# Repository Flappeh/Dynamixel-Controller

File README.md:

# Custom-Dynamixel-Controller
ESP32 Based Dynamixel Controller for MX-Series

This is a Custom Controller for Dynamixel MX-Series Servos that uses Dynamixel Protocol 1.0.

This Project Consists of 3 main components:
1. PCB

2. ESP32 Custom Firmware
3. .NET Core 3 Application

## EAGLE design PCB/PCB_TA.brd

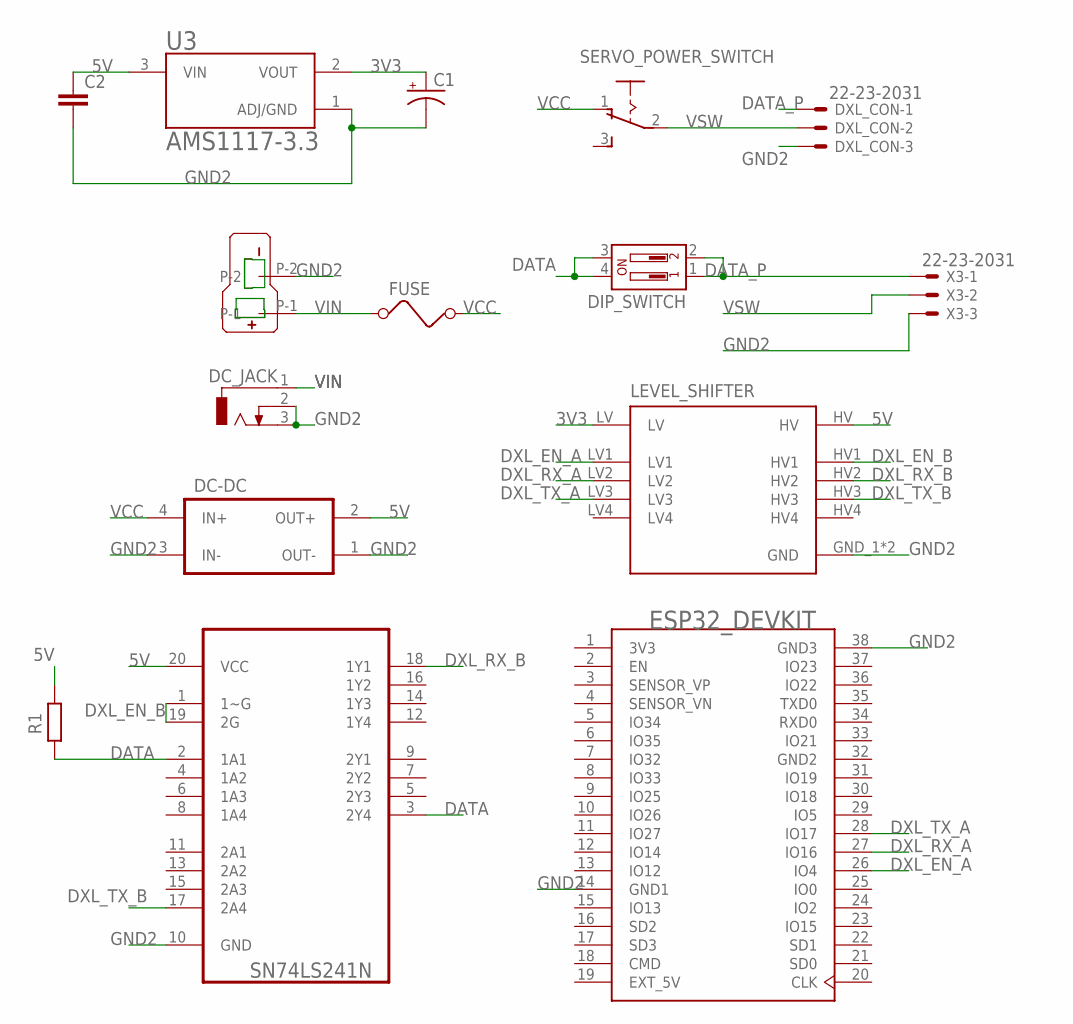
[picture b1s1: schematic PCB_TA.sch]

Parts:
BUCK_CONVERTER: DC-DC_CONV
C1: CPOL-USE3.5-8; E3,5-8
C2: C-EU025-025X050; C025-025X050
DC_JACK: DCJ0202
DIP_SWITCH: DIP-02-PTH-100MIL; DIPSWITCH-02-209-2LPST
DXL_CON: 22-23-2031
ESP32_DEVKIT: ESP32-DEVKITC; MODULE_ESP32-DEVKITC
FUSE: FUSE
LEVEL_SHIFTER: BOB-12009; CONV_BOB-12009
R1: R-EU_R0805; R0805
SERVO_POWER_SWITCH: 255SB
U2: SN74LS241N; DIP254P762X508-20
U3: AMS1117-3.3; SOT229P700X180-4N
U$1: T-PLUG_CONNECTOR; T_PLUG_CONNECTOR
X3: 22-23-2031

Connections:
3V3: C1.+, ESP32_DEVKIT.1 (3V3), LEVEL_SHIFTER.LV, U3.2 (VOUT)
5V: BUCK_CONVERTER.2 (OUT+), C2.1, LEVEL_SHIFTER.HV, R1.1, U2.20 (VCC), U3.3 (VIN)
DATA: DIP_SWITCH.3, DIP_SWITCH.4, R1.2, U2.2 (1A1), U2.3 (2Y4)
DATA_P: DIP_SWITCH.1, DIP_SWITCH.2, DXL_CON.1, X3.1
DXL_EN_A: ESP32_DEVKIT.26 (IO4), LEVEL_SHIFTER.LV1
DXL_EN_B: LEVEL_SHIFTER.HV1, U2.1 (1~G), U2.19 (2G)
DXL_RX_A: ESP32_DEVKIT.27 (IO16), LEVEL_SHIFTER.LV2
DXL_RX_B: LEVEL_SHIFTER.HV2, U2.18 (1Y1)
DXL_TX_A: ESP32_DEVKIT.28 (IO17), LEVEL_SHIFTER.LV3
DXL_TX_B: LEVEL_SHIFTER.HV3, U2.17 (2A4)
EXT_5V: ESP32_DEVKIT.19 (EXT_5V)
GND2: BUCK_CONVERTER.1 (OUT-), BUCK_CONVERTER.3 (IN-), C1.-, C2.2, DC_JACK.2, DC_JACK.3, DXL_CON.3, ESP32_DEVKIT.14 (GND1), ESP32_DEVKIT.32 (GND2), ESP32_DEVKIT.38 (GND3), LEVEL_SHIFTER.GND_1 (GND), LEVEL_SHIFTER.GND_2 (GND), U2.10 (GND), U3.1 (ADJ/GND), U$1.P-2, X3.3
VCC: BUCK_CONVERTER.4 (IN+), FUSE.2, SERVO_POWER_SWITCH.1 (O)
VIN: DC_JACK.1, FUSE.1, U$1.P-1
VSW: DXL_CON.2, SERVO_POWER_SWITCH.2, X3.2

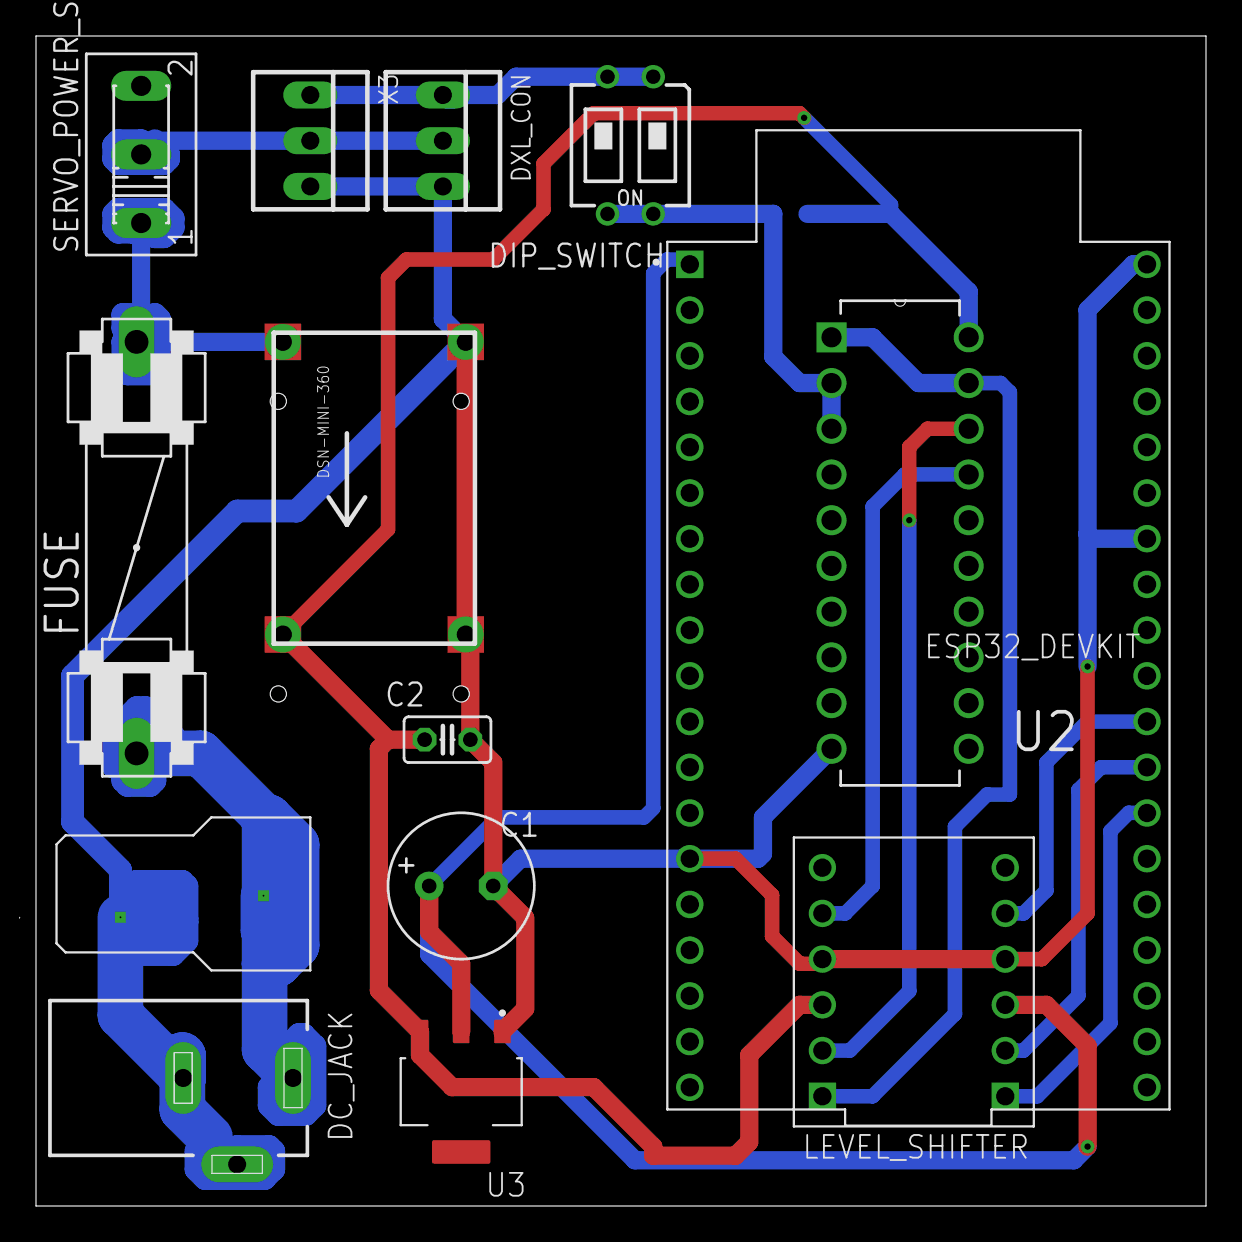
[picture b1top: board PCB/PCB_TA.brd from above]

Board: 2 copper layers, 65.0 x 65.0 mm, 15 parts (1 on the bottom side), 14 nets.

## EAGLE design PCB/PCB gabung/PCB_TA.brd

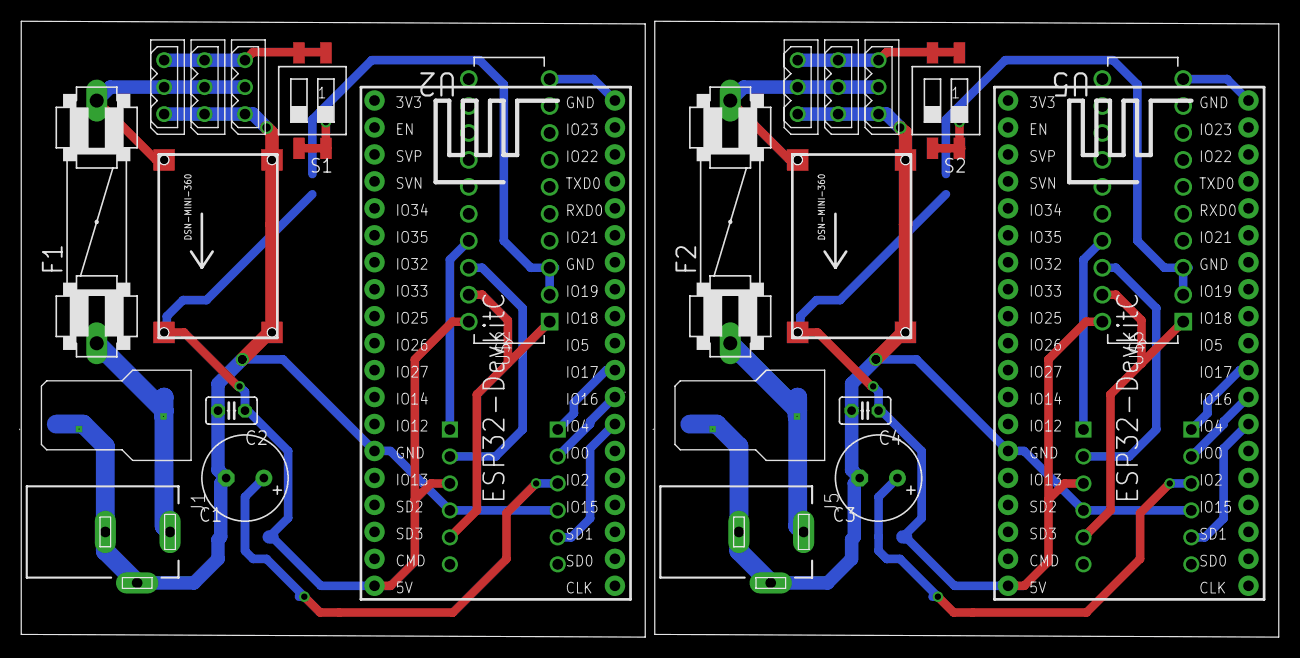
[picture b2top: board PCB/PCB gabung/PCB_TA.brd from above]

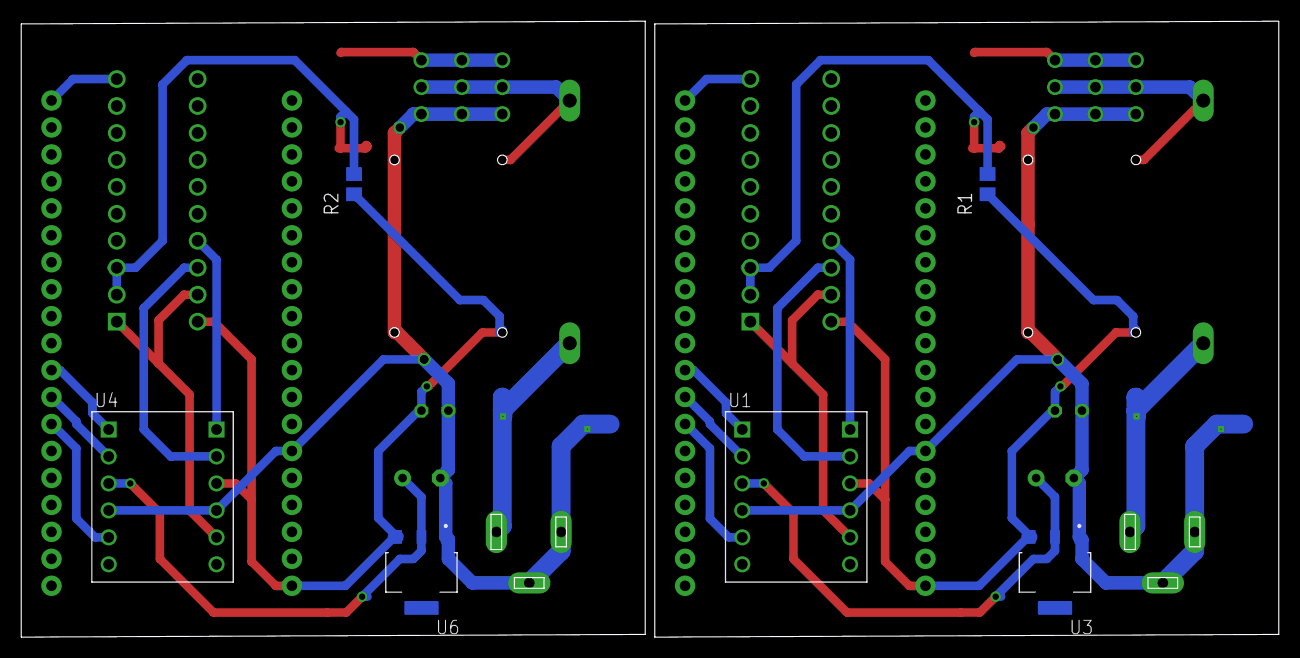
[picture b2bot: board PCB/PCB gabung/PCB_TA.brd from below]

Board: 2 copper layers, 118.5 x 58.0 mm, 30 parts (6 on the bottom side), 26 nets.

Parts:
C1, C3: E3,5-8
C2, C4: C025-025X050
F1, F2: FUSE
J1, J5: DCJ0202
J2, J3, J4, J6, J7, J8: 22-03-5035; 5267-3
R1, R2: R0805
S1, S2: SWS002; SMS-002
U1, U4: BOB-12009; CONV_BOB-12009
U2, U5: SN74LS241N; DIP254P762X508-20
U3, U6: AMS1117-3.3; SOT229P700X180-4N
U$1, U$4: T-PLUG_CONNECTOR; T_PLUG_CONNECTOR
U$2, U$5: ESP32DEVKITC; ESP32-DEVKITC
U$3, U$6: DC-DC_CONV

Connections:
3V1: C3.+, U4.LV, U6.2
3V3: C1.+, U1.LV, U3.2
5V: C2.1, R1.1, U1.HV, U2.20, U3.3, U$2.19, U$3.2
5V1: C4.1, R2.1, U4.HV, U5.20, U6.3, U$5.19, U$6.2
DATA: R1.2, S1.4, U2.2, U2.3
DATA1: R2.2, S2.4, U5.2, U5.3
DATA_P: J2.3, J3.3, J4.3, S1.1
DATA_P1: J6.3, J7.3, J8.3, S2.1
DXL_EN_A: U1.LV3, U$2.26
DXL_EN_A1: U4.LV3, U$5.26
DXL_EN_B: U1.HV3, U2.1, U2.19
DXL_EN_B1: U4.HV3, U5.1, U5.19
DXL_RX_A: U1.LV2, U$2.27
DXL_RX_A1: U4.LV2, U$5.27
DXL_RX_B: U1.HV2, U2.18
DXL_RX_B1: U4.HV2, U5.18
DXL_TX_A: U1.LV1, U$2.28
DXL_TX_A1: U4.LV1, U$5.28
DXL_TX_B: U1.HV1, U2.17
DXL_TX_B1: U4.HV1, U5.17
GND1: C3.-, C4.2, J5.2, J5.3, J6.1, J7.1, J8.1, U4.GND_1, U4.GND_2, U5.10, U6.1, U$4.P-2, U$5.14, U$5.38, U$6.1, U$6.3
GND2: C1.-, C2.2, J1.2, J1.3, J2.1, J3.1, J4.1, U1.GND_1, U1.GND_2, U2.10, U3.1, U$1.P-2, U$2.14, U$2.38, U$3.1, U$3.3
VCC: F1.2, J2.2, J3.2, J4.2, U$3.4
VCC1: F2.2, J6.2, J7.2, J8.2, U$6.4
VIN: F1.1, J1.1, U$1.P-1
VIN1: F2.1, J5.1, U$4.P-1

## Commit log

2022-08-19 Addition of every local files
2022-09-13 Restructured folder format
2022-09-13 add image for Application
2022-09-13 README update

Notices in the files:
parts and their libraries:
SparkFun-Switches: Licensing: Creative Commons ShareAlike 4.0 International - https://creativecommons.org/licenses/by-sa/4.0
